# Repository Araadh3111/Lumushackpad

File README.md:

# Lumuspad

A 5-key macropad with a rotary encoder, OLED screen and RGB underglow.
Based on HackClub's MacroPad Guide: https://hackpad.hackclub.com/guide

----------------------------------
What it does:-

- SW1: New tab (Ctrl+T)
- SW2: Cycles the OLED animation (Cyberpunk scanner / Equalizer / Stealth logo)
- SW3: Launches VS Code
- SW4: Opens YouTube in Brave
- SW5: Leaves the current call (Zoom / Teams / Discord)
- Knob: Volume up/down, press to mute
- 5x SK6812 RGB LEDs running a rainbow swirl

----------------------------------
File Structure:-

--CAD

  -luma_bottom_tray.step

  -luma_spacer.step

  -luma_switch_plate.step

  -luma_case_assembled.step

--Firmware (QMK, builds automatically via GitHub Actions -> .uf2)

  -keyboard.json

  -keymap.c

  -config.h

  -rules.mk

--PCB (schematics + pcb)

  -Luma pcb.kicad_pro / .kicad_sch / .kicad_pcb

----------------------------------
Schematic:-

Heres my schematic I forgot to organise :(

PCB:-
Here is my pcb I imported the silkscreen from pinterest then used inbuilt image converter to copy it and paste it on the pcb

PS:- the led dioded do not intersect with the switch as they are inverted and on the other side! more can be seen from the next two screenshots

Case:-
here is my case, I was aiming for one cyberpunkish case and made it its screwable from the corners(m3 screws)

Assembled:-
here is the assembled file! (ps: the pins will be bended!)

---------------------------------
Ai usage:-
I used claude to help me make the qmk firmware! rest build was done by me
----------------------------------
BOM:-

-1x Seeed XIAO RP2040

-5x MX-style Switches

-5x DSA Keycaps

-1x EC11 Rotary Encoder (with push button)

-1x 0.91" 128x32 OLED Display (I2C)

-5x SK6812 MINI RGB LEDs

-1x Resistor (RGB data line)

-5x 100nF Capacitors and one μF Capacitor in the pcb

-1x Case (3 printed parts: bottom tray, spacer, switch plate)

No diodes needed — every switch has its own pin (direct wiring).

refer to BOM.CSV
+ pcb printing fund

----------------------------------
Firmware:-

Compiled automatically by GitHub Actions on every push.
Grab the latest lumuspad_firmware artifact from the Actions tab,
hold the BOOT button on the XIAO while plugging in USB,
and drag the .uf2 onto the RPI-RP2 drive.
----------------------------------

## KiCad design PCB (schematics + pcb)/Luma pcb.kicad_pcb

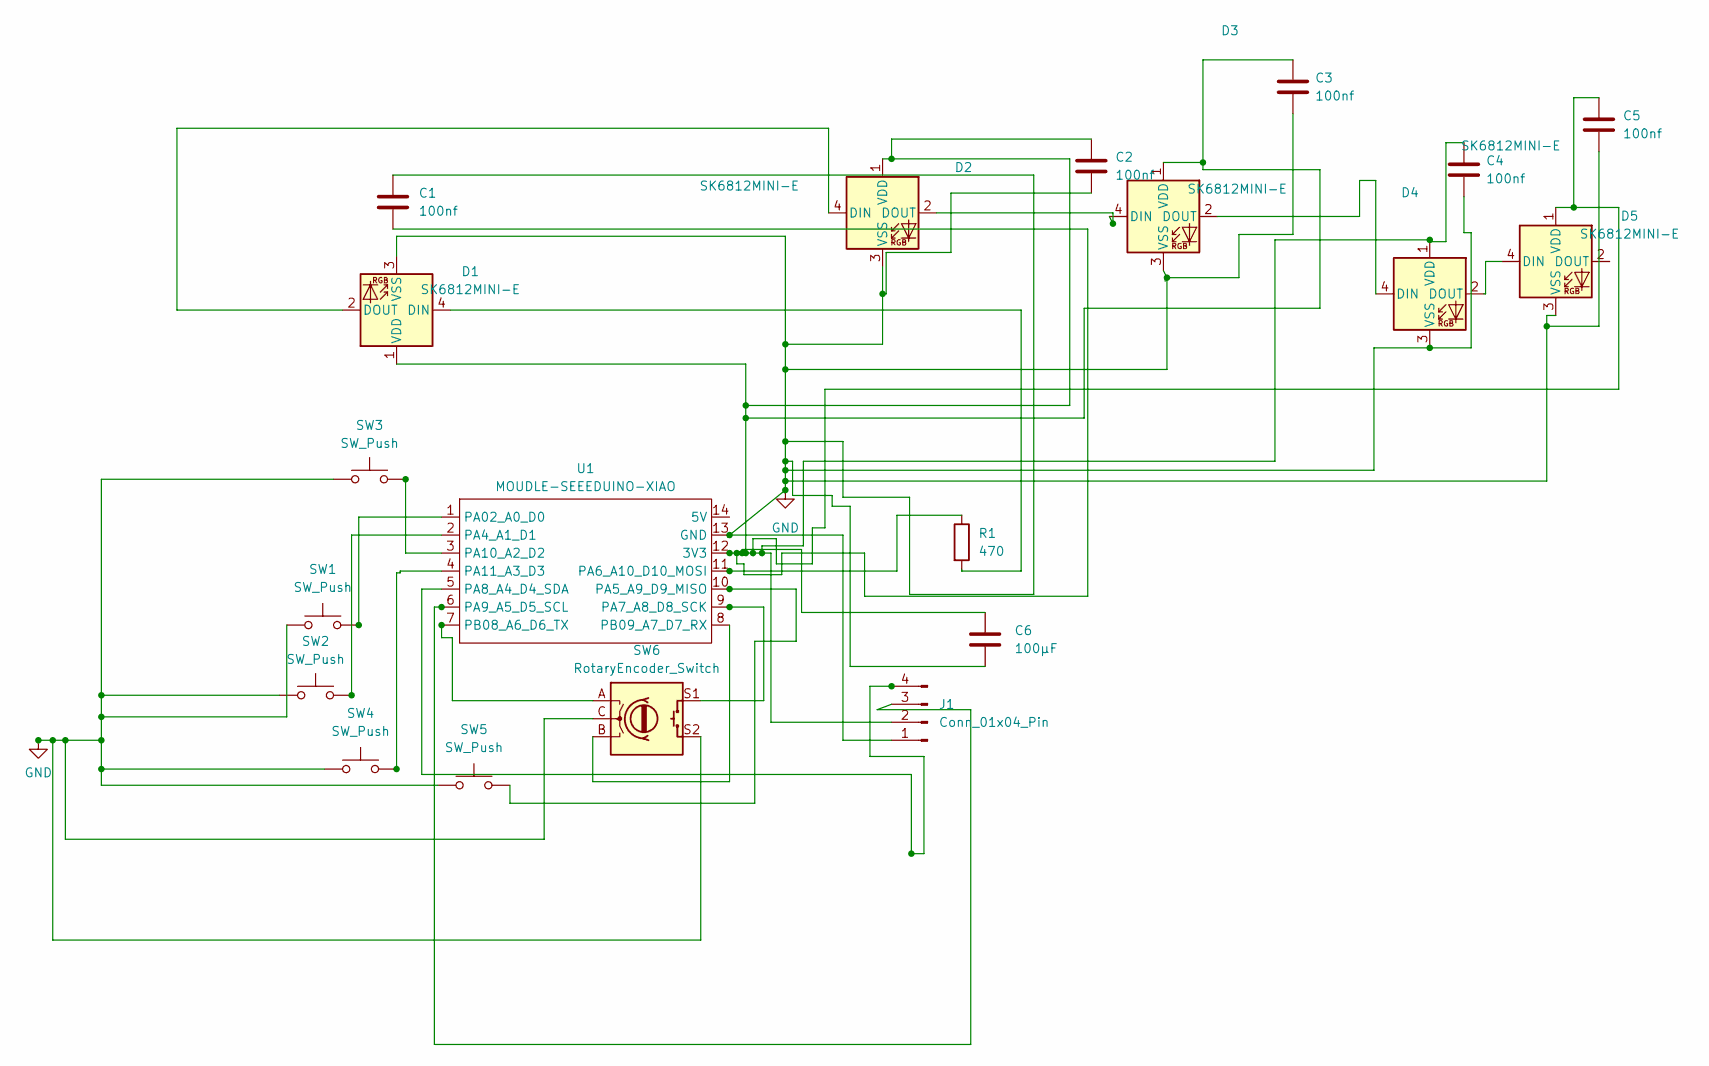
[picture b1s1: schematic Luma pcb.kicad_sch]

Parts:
C1, C2, C3, C4, C5: 100nf; C_0805_2012Metric_Pad1.18x1.45mm_HandSolder
C6: 100µF; CP_Radial_D5.0mm_P2.00mm
D1, D2, D3, D4, D5: SK6812MINI-E; SK6812MINI-E_fixed
J1: Conn_01x04_Pin; FanPinHeader_1x04_P2.54mm_Vertical
R1: 470; R_Axial_DIN0207_L6.3mm_D2.5mm_P7.62mm_Horizontal
SW1, SW2, SW3, SW4, SW5: SW_Push; SW_Cherry_MX_1.00u_PCB
SW6: RotaryEncoder_Switch; RotaryEncoder_Alps_EC11E-Switch_Vertical_H20mm
U1: MOUDLE-SEEEDUINO-XIAO; XIAO-Generic-Hybrid-14P-2.54-21X17.8MM

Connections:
GND: C1.1, C2.2, C3.2, C4.2, C5.2, C6.2, D1.3 (VSS), D2.3 (VSS), D3.3 (VSS), D4.3 (VSS), D5.3 (VSS), J1.1, SW1.1, SW2.1, SW3.1, SW4.1, SW5.1, SW6.C, SW6.S2, U1.13 (GND)
unnamed: D1.4 (DIN), R1.2
unnamed: D1.2 (DOUT), D2.4 (DIN)
unnamed: C1.2, C2.1, C3.1, C4.1, C5.1, C6.1, D1.1 (VDD), D2.1 (VDD), D3.1 (VDD), D4.1 (VDD), D5.1 (VDD), J1.2, U1.12 (3V3)
unnamed: D2.2 (DOUT), D4.4 (DIN)
unnamed: D3.4 (DIN), D4.2 (DOUT)
unnamed: D3.2 (DOUT), D5.4 (DIN)
unnamed: J1.3, U1.6 (PA9_A5_D5_SCL)
unnamed: J1.4, U1.5 (PA8_A4_D4_SDA)
unnamed: SW1.2, U1.1 (PA02_A0_D0)
unnamed: SW2.2, U1.2 (PA4_A1_D1)
unnamed: SW5.2, U1.10 (PA5_A9_D9_MISO)
unnamed: R1.1, U1.11 (PA6_A10_D10_MOSI)
unnamed: SW6.S1, U1.9 (PA7_A8_D8_SCK)
unnamed: SW3.2, U1.3 (PA10_A2_D2)
unnamed: SW4.2, U1.4 (PA11_A3_D3)
unnamed: SW6.A, U1.7 (PB08_A6_D6_TX)
unnamed: SW6.B, U1.8 (PB09_A7_D7_RX)

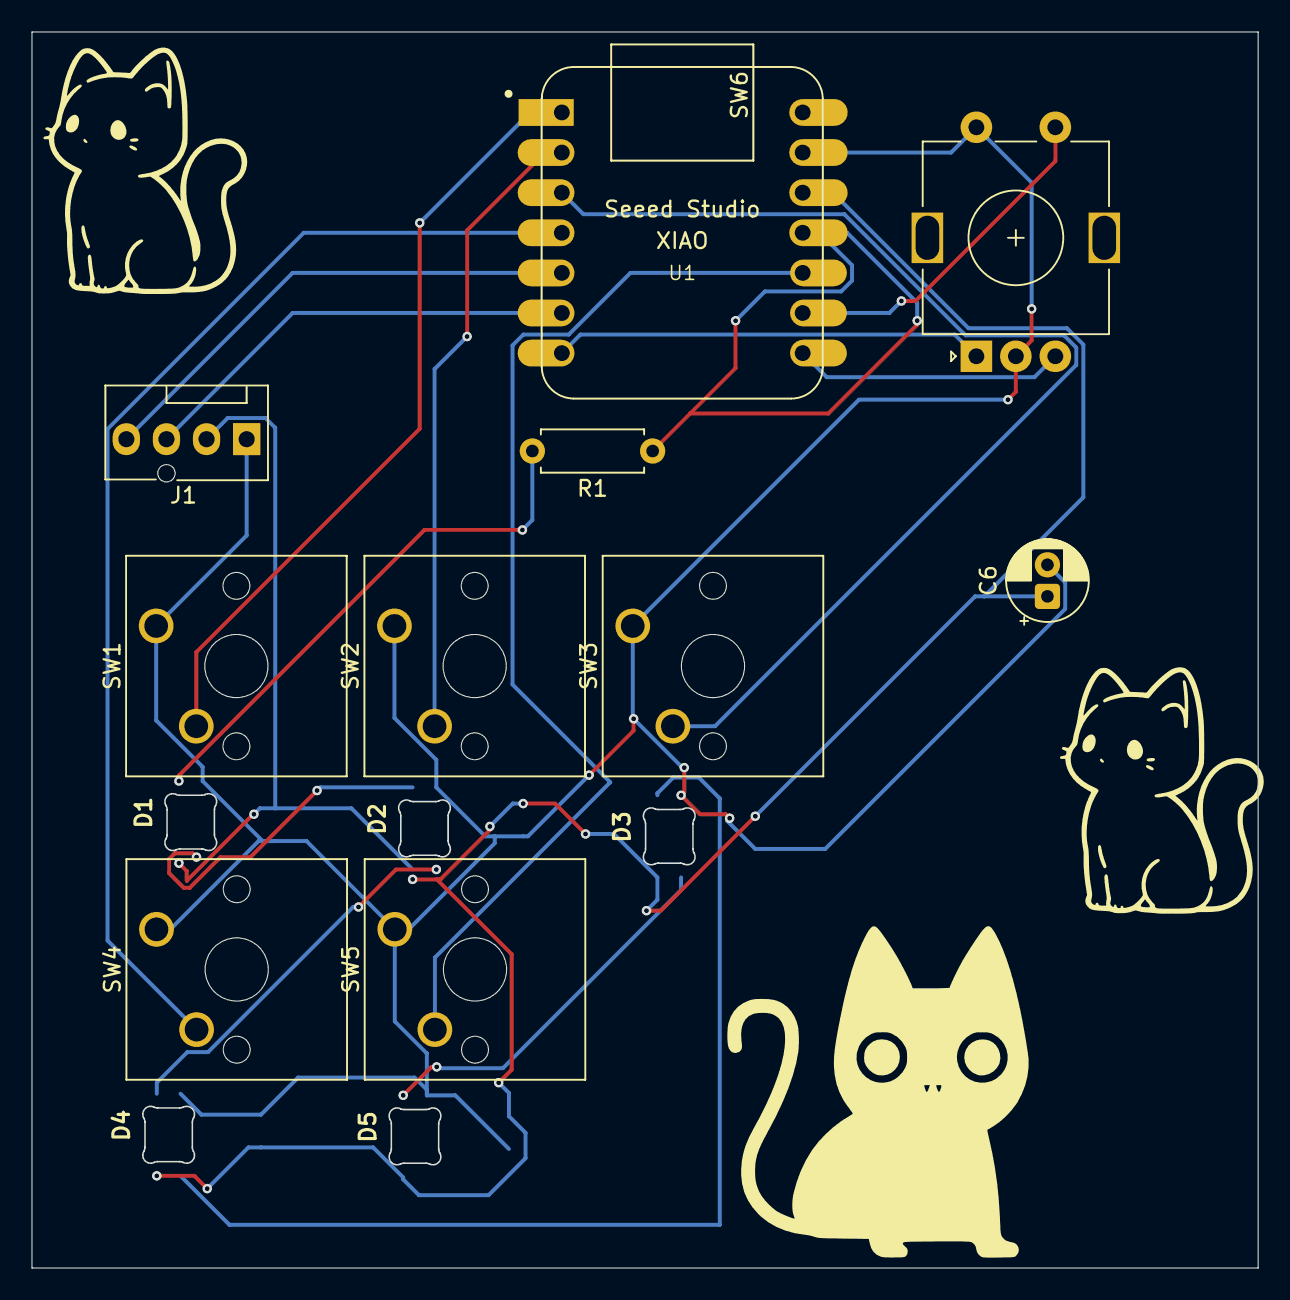
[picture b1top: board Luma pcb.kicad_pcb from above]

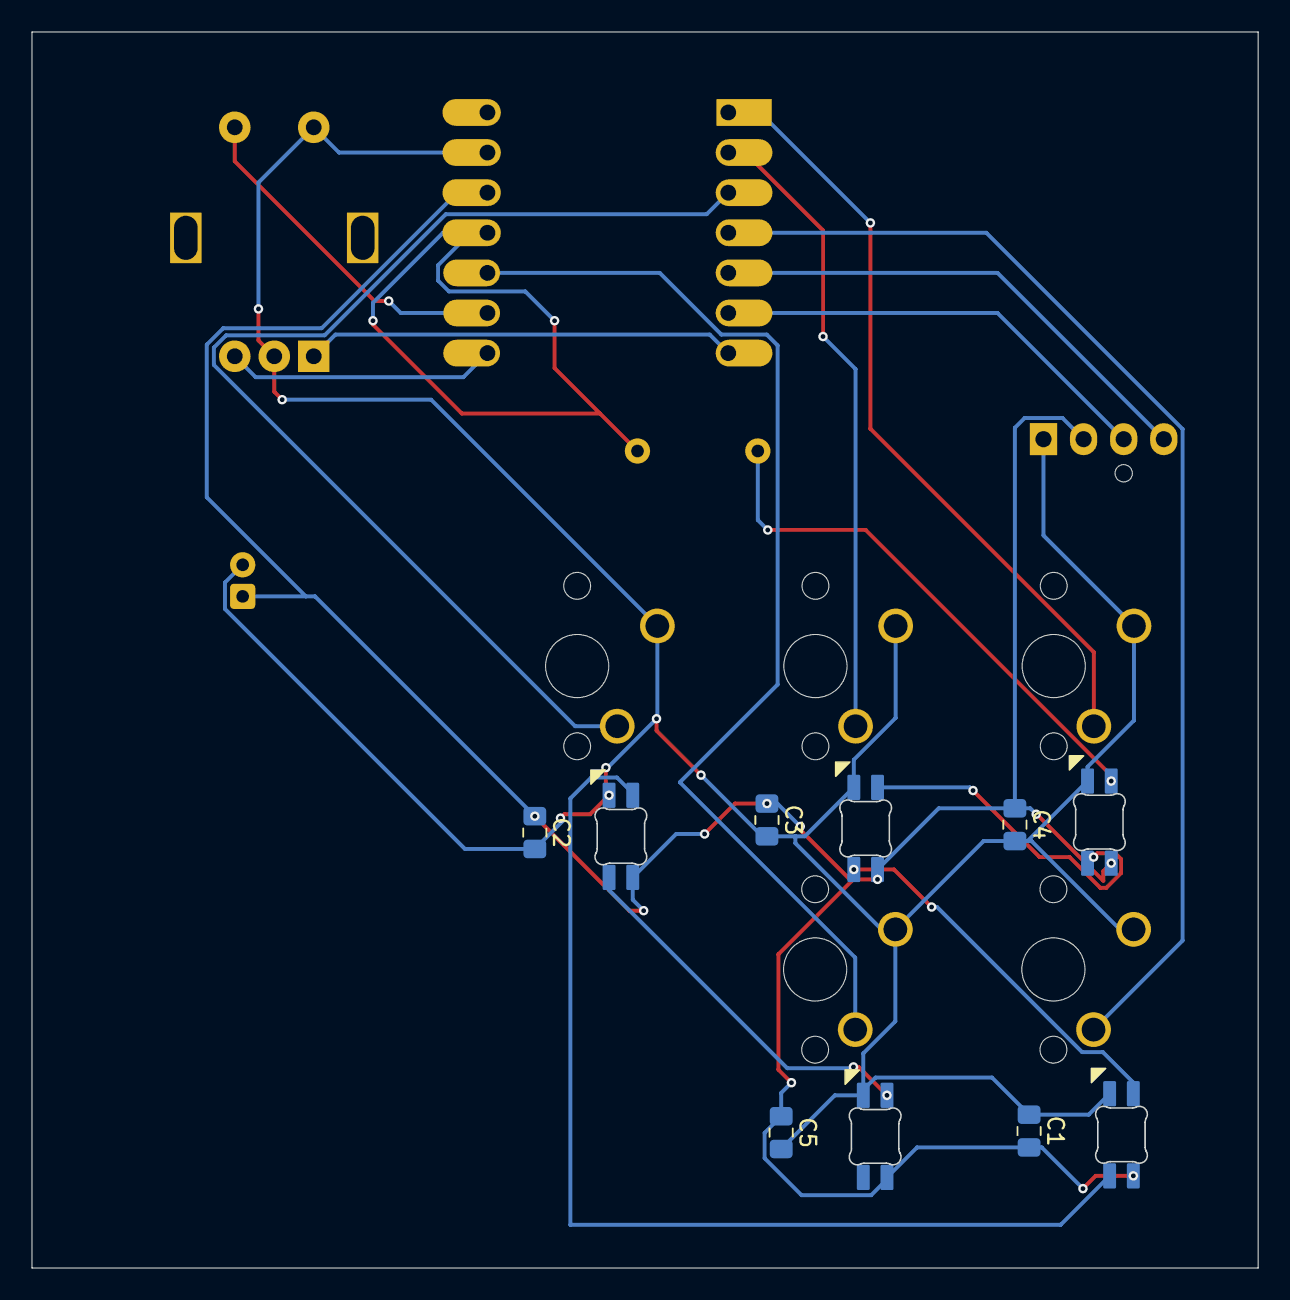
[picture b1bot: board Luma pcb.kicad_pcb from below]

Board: 2 copper layers, 77.6 x 78.3 mm, 20 parts (5 on the bottom side), 18 nets.

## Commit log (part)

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2026-06-08 Initial commit: Completed schematics and initial PCB footprint layout
2026-06-08 Add KiCad backup and temporary files to .gitignore
2026-06-12 Add images for schematic, PCB, and case in README
    Updated README.md to include schematic, PCB, and case images.
2026-06-12 Update PCB design
2026-06-12 Add production folder
2026-06-12 Revise README.md for clarity and details
    Updated descriptions for schematic, PCB, and case sections. Clarified capacitor count in the components list.
2026-06-12 added text to the bottom tray
2026-06-12 added small changes to pcb
2026-06-17 Update README with PCB printing fund information
    Added section about PCB printing fund to README.
2026-06-29 Add BOM entries for components and quantities
2026-06-29 added BOM
